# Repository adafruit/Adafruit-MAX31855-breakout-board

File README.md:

# Adafruit MAX31855 Thermocouple Amp breakout

<a href="http://www.adafruit.com/products/269"><br/>Click here to purchase one from the Adafruit shop</a>

Thermocouples are very sensitive, requiring a good amplifier with a cold-compensation reference. The MAX31855K does everything for you, and can be easily interfaced with any microcontroller, even one without an analog input. This breakout board has the chip itself, a 3.3V regulator with 10uF bypass capacitors and level shifting circuitry, all assembled and tested. Comes with a 2 pin terminal block (for connecting to the thermocouple) and pin header (to plug into any breadboard or perfboard). [Goes great with our 1m K-type thermocouple](http://www.adafruit.com/products/270).

[If you need a thermocouple interface that can handle other types of thermocouples, check out our 'Universal' MAX31856 amplifier board which can be configured in the Arduino sketch to interface with just about any kind of thermocouple](https://www.adafruit.com/products/3263)

## License

Adafruit invests time and resources providing this open source design, 
please support Adafruit and open-source hardware by purchasing 
products from Adafruit!

All text above must be included in any redistribution

Designed by Limor Fried/Ladyada for Adafruit Industries.
Creative Commons Attribution/Share-Alike, all text above must be included in any redistribution

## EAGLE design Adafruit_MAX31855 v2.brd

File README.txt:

Adafruit MAX31885 Thermocouple Amp breakout

These are the Eagle CAD files for the Adafruit MAX31885 Thermocouple Amp breakout:
  ----> http://www.adafruit.com/products/269

Adafruit invests time and resources providing this open source design, please support Adafruit and open-source hardware by purchasing products from Adafruit!

Thermocouples are very sensitive, requiring a good amplifier with a cold-compensation reference. The MAX31855K does everything for you, and can be easily interfaced with any microcontroller, even one without an analog input. This breakout board has the chip itself, a 3.3V regulator with 10uF bypass capacitors and level shifting circuitry, all assembled and tested. Comes with a 2 pin terminal block (for connecting to the thermocouple) and pin header (to plug into any breadboard or perfboard). Goes great with our 1m K-type thermocouple. 

All text above must be included in any redistribution

Designed by Limor Fried/Ladyada for Adafruit Industries.
Creative Commons Attribution/Share-Alike, all text above must be included in any redistribution

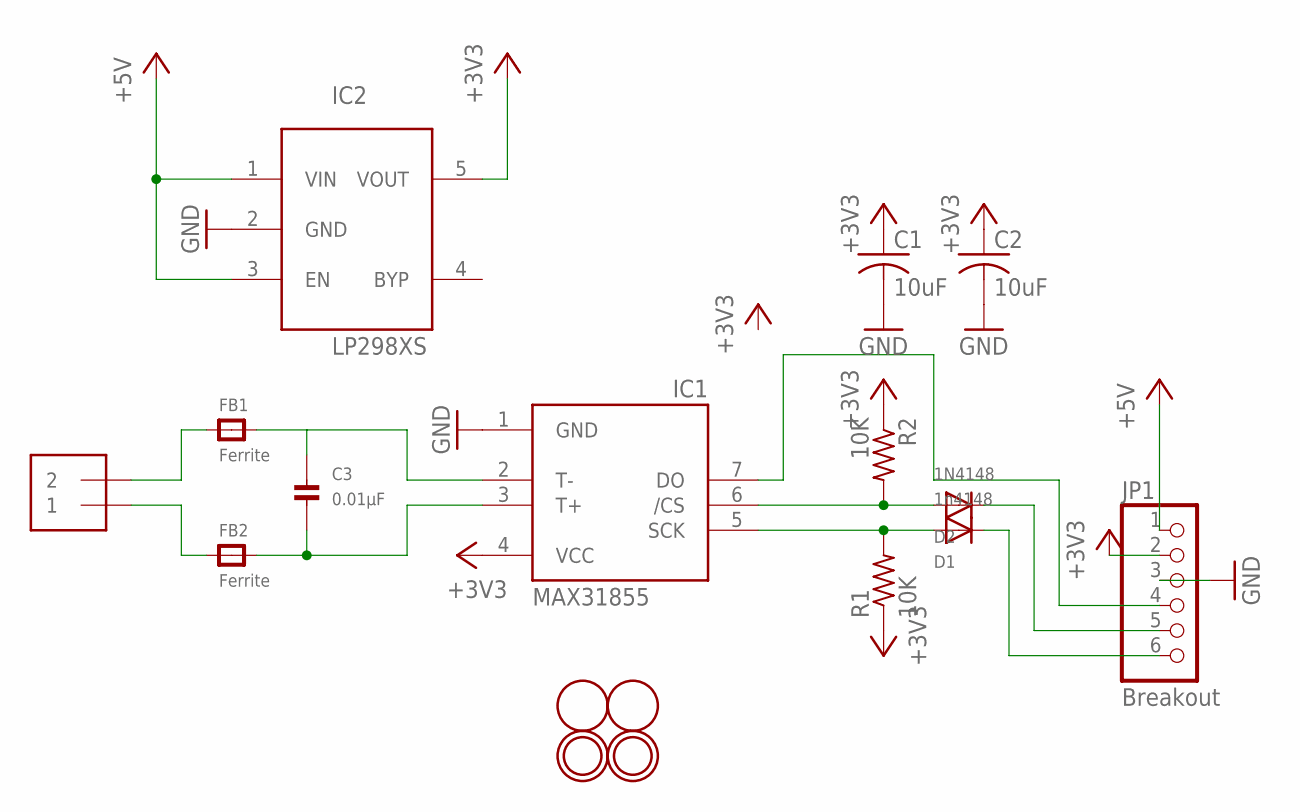
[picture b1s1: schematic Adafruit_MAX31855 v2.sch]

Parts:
C1, C2: 10uF; C0805K
C3: 0.01µF; _0805
D1: 1n4148; SOD-323F
D2: 1N4148; SOD-323F
FB1, FB2: Ferrite; _0805
IC1: MAX31855; SO08
IC2: LP298XS; SOT23-5L
J1: 1X2-3.5MM
JP1: Breakout; 1X06_ROUND_76
R1, R2: 10K; R0805
U$1, U$2: FIDUCIAL; FIDUCIAL_1MM
U$4, U$5: MOUNTINGHOLE2.0; MOUNTINGHOLE_2.0_PLATED

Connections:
+3V3: C1.1, C2.1, IC1.4 (VCC), IC2.5 (VOUT), JP1.2, R1.1, R2.1
+5V: IC2.1 (VIN), IC2.3 (EN), JP1.1
CS: D2.A, IC1.6 (/CS), R2.2
DO: IC1.7 (DO), JP1.4
GND: C1.2, C2.2, IC1.1 (GND), IC2.2 (GND), JP1.3
unnamed: FB1.1, J1.2
unnamed: D2.C, JP1.5
unnamed: D1.C, JP1.6
unnamed: C3.1, FB1.2, IC1.2 (T-)
unnamed: FB2.1, J1.1
unnamed: C3.2, FB2.2, IC1.3 (T+)
SCK: D1.A, IC1.5 (SCK), R1.2

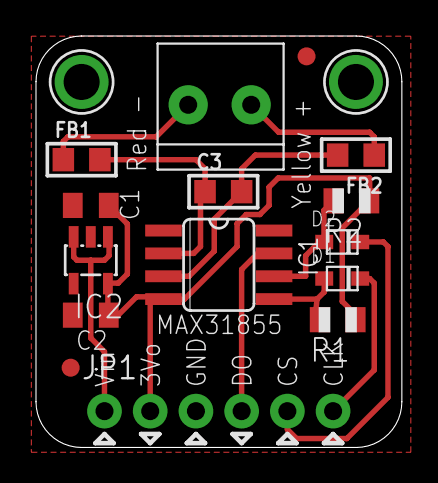
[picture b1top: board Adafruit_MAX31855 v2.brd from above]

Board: 2 copper layers, 20.3 x 22.9 mm, 18 parts (1 on the bottom side), 12 nets.

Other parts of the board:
U$6: ADAFRUIT_3.5MM

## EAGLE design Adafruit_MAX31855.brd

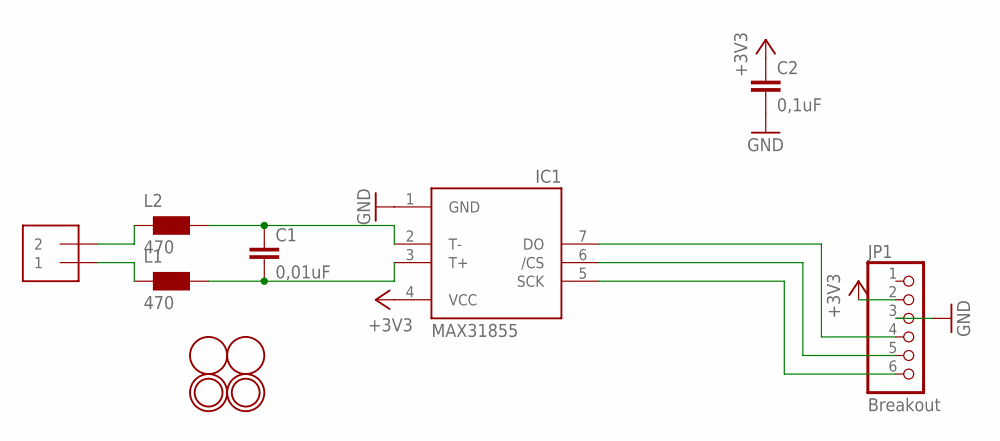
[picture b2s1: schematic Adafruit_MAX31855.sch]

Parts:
C1: 0,01uF; C0805K
C2: 0,1uF; C0805K
IC1: MAX31855; SO08
J1: 1X2-3.5MM
JP1: Breakout; 1X06_ROUND_76
L1, L2: 470; 0805
U$1, U$2: FIDUCIAL; FIDUCIAL_1MM
U$4, U$5: MOUNTINGHOLE2.0; MOUNTINGHOLE_2.0_PLATED

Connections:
+3V3: C2.1, IC1.4 (VCC), JP1.2
DO: IC1.7 (DO), JP1.4
GND: C2.2, IC1.1 (GND), JP1.3
unnamed: J1.2, L2.1
unnamed: IC1.6 (/CS), JP1.5
unnamed: IC1.5 (SCK), JP1.6
unnamed: C1.1, IC1.2 (T-), L2.2
unnamed: J1.1, L1.1
unnamed: C1.2, IC1.3 (T+), L1.2

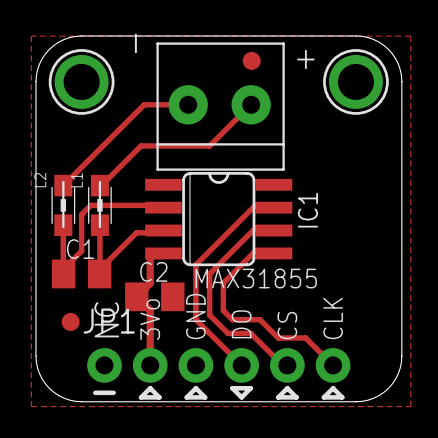
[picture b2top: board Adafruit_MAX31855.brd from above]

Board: 2 copper layers, 20.3 x 20.3 mm, 12 parts (1 on the bottom side), 9 nets.

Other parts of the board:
U$6: ADAFRUIT_3.5MM

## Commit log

2012-05-25 init
2012-05-25 read
2012-09-11 Update
    - Removed the 3.3V regulator from the design to make it cheaper.
    - Reviewed Maxim's protoboard and added ferrite cores and capacitor for
    better signal stability.
    Boards can be orderd cheap from http://www.seeedstudio.com.
    Perfect for Raspberry Pi
    Hope you like it!
2013-06-11 version 2 files!
2019-04-25 readme + image
2019-04-25 image replacement
2019-04-25 readme update
2019-05-16 added license
2019-10-07 Fix typo in title
    The title refers to MAX31885, should be 31855
